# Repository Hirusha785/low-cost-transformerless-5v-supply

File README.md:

# Low-Cost Transformerless 5V Supply

A compact **non-isolated transformerless AC-to-5V DC power supply PCB** designed using KiCad.

This project uses a capacitive dropper circuit, bridge rectifier, smoothing capacitors, zener protection, and an LM7805 voltage regulator to generate a low-current 5V DC output.

> ⚠️ **High Voltage Warning:**  
> This is a **non-isolated mains-powered circuit**. The 5V output is **not safely isolated** from AC mains.  
> Do not touch the circuit while powered. Do not connect it to USB, computers, Arduino boards, ESP32 boards, oscilloscopes, or any user-accessible circuit unless proper isolation is added.

---

## Repository Description

A compact non-isolated transformerless AC-to-5V DC power supply PCB using a capacitive dropper, bridge rectifier, zener protection, 7805 regulator, and LED power indicator.

---

## Project Overview

This PCB demonstrates a low-cost transformerless power supply design suitable for learning, testing, and sealed low-power applications.

The circuit converts AC mains input into regulated 5V DC through the following stages:

1. Capacitive voltage/current dropping stage
2. Bridge rectifier stage
3. DC smoothing and filtering stage
4. Zener overvoltage protection stage
5. 7805 linear voltage regulation stage
6. LED power indication stage

---

## Features

- Low-cost transformerless AC-to-DC design
- Compact PCB layout
- 5V regulated DC output
- Bridge rectifier using 1N4007 diodes
- Zener diode voltage protection
- LM7805 / 7805 TO-220 voltage regulator
- LED power indicator
- Screw terminal AC input
- Screw terminal 5V DC output
- Through-hole component design
- Designed in KiCad

---

## Circuit Operation 

AC mains input is connected through J1.
C4 works as the capacitive dropper and limits the input current.
R3 discharges C4 after power is removed.
D1–D4 form the bridge rectifier and convert AC to DC.
C1 filters high-frequency noise.
C2 smooths the rectified DC voltage and reduces ripple.
D5 and D6 provide Zener voltage protection/clamping.
R1 and R2 help limit current in the protection stage.
U1 is the 7805 voltage regulator and provides regulated 5V DC output.
C5 smooths the final 5V output.
D7 and R4 work as the power indicator circuit.
Since this is a transformerless design, the output is not isolated from AC mains and must be handled carefully.

---

## Main Components

| Reference | Component | Description |
|---|---|---|
| J1 | Screw Terminal | AC input connector |
| C4 | 225k / 2.2uF Capacitor | Capacitive dropper capacitor |
| R3 | 1MΩ | Dropper capacitor discharge resistor |
| D1 | 1N4007 | Bridge rectifier diode |
| D2 | 1N4007 | Bridge rectifier diode |
| D3 | 1N4007 | Bridge rectifier diode |
| D4 | 1N4007 | Bridge rectifier diode |
| C1 | 0.1uF | Noise filtering capacitor |
| C2 | 1000uF | DC smoothing capacitor |
| D5 | Zener Diode | Voltage protection/clamping |
| D6 | Zener Diode | Voltage protection/clamping |
| R1 | 20kΩ | Protection/bias resistor |
| R2 | 20kΩ | Protection/bias resistor |
| U1 | LM7805 / 7805 TO-220 | 5V voltage regulator |
| C5 | 470uF | Output smoothing capacitor |
| D7 | LED | Power indicator |
| R4 | 2.2kΩ | LED current-limiting resistor |
| J2 | Screw Terminal | 5V DC output connector |

---

## PCB Design

The PCB was designed using KiCad and includes:

- Through-hole components
- AC input screw terminal
- 5V DC output screw terminal
- Compact board layout
- Top and bottom routing
- 3D model preview
- Power indicator LED
- Mounting holes

---

## Project Images

### Circuit Schematic

---

### PCB Layout

---

### 3D View

---

## Suitable Applications

This circuit may only be used in **sealed low-power applications**, such as:

- 💡 **Small indicator circuits**  
  For basic power indication or low-current status indication circuits inside closed equipment.

- 🔧 **Low-current control circuits**  
  For small internal control circuits where only a limited amount of current is required.

- 📦 **Enclosed appliance control boards**  
  Suitable only when the full PCB is mounted inside a properly insulated and sealed enclosure.

- 🎓 **Educational PCB design demonstrations**  
  Useful for learning about capacitive dropper supplies, rectification, filtering, zener protection, and basic voltage regulation.

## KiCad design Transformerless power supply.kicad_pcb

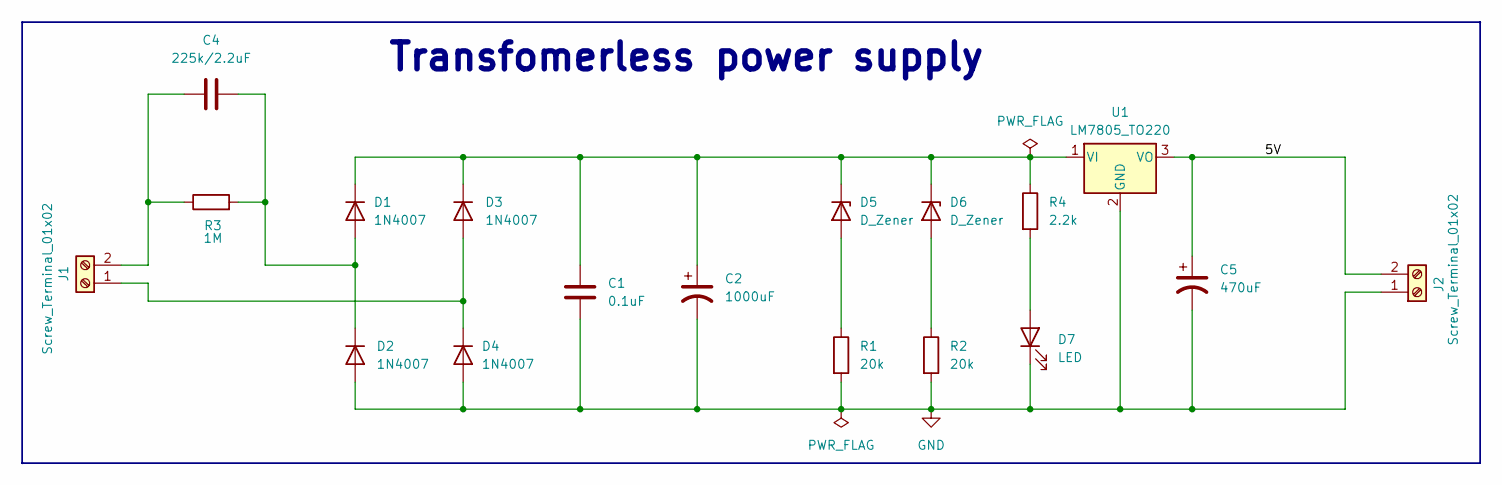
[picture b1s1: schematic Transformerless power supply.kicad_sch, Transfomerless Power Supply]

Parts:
C1: 0.1uF; C_Disc_D4.7mm_W2.5mm_P5.00mm
C2: 1000uF; CP_Radial_D10.0mm_P5.00mm
C4: 225k/2.2uF; C_Rect_L18.0mm_W6.0mm_P15.00mm_FKS3_FKP3
C5: 470uF; CP_Radial_D10.0mm_P5.00mm
D1, D2, D3, D4: 1N4007; D_DO-41_SOD81_P10.16mm_Horizontal
D5, D6: D_Zener; D_A-405_P7.62mm_Horizontal
D7: LED; LED_D5.0mm
J1, J2: Screw_Terminal_01x02; TerminalBlock_bornier-2_P5.08mm
R1, R2: 20k; R_Axial_DIN0207_L6.3mm_D2.5mm_P7.62mm_Horizontal
R3: 1M; R_Axial_DIN0207_L6.3mm_D2.5mm_P7.62mm_Horizontal
R4: 2.2k; R_Axial_DIN0207_L6.3mm_D2.5mm_P7.62mm_Horizontal
U1: LM7805_TO220; TO-220-3_Vertical

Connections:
/5V: C5.1, J2.2, U1.3 (VO)
GND: C1.2, C2.2, C5.2, D2.2 (A), D4.2 (A), D7.1 (K), J2.1, R1.2, R2.2, U1.2 (GND)
unnamed: C4.1, D1.2 (A), D2.1 (K), R3.2
unnamed: C1.1, C2.1, D1.1 (K), D3.1 (K), D5.1 (K), D6.1 (K), R4.1, U1.1 (VI)
unnamed: D3.2 (A), D4.1 (K), J1.1
unnamed: D5.2 (A), R1.1
unnamed: D6.2 (A), R2.1
unnamed: D7.2 (A), R4.2
unnamed: C4.2, J1.2, R3.1

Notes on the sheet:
Transfomerless power supply

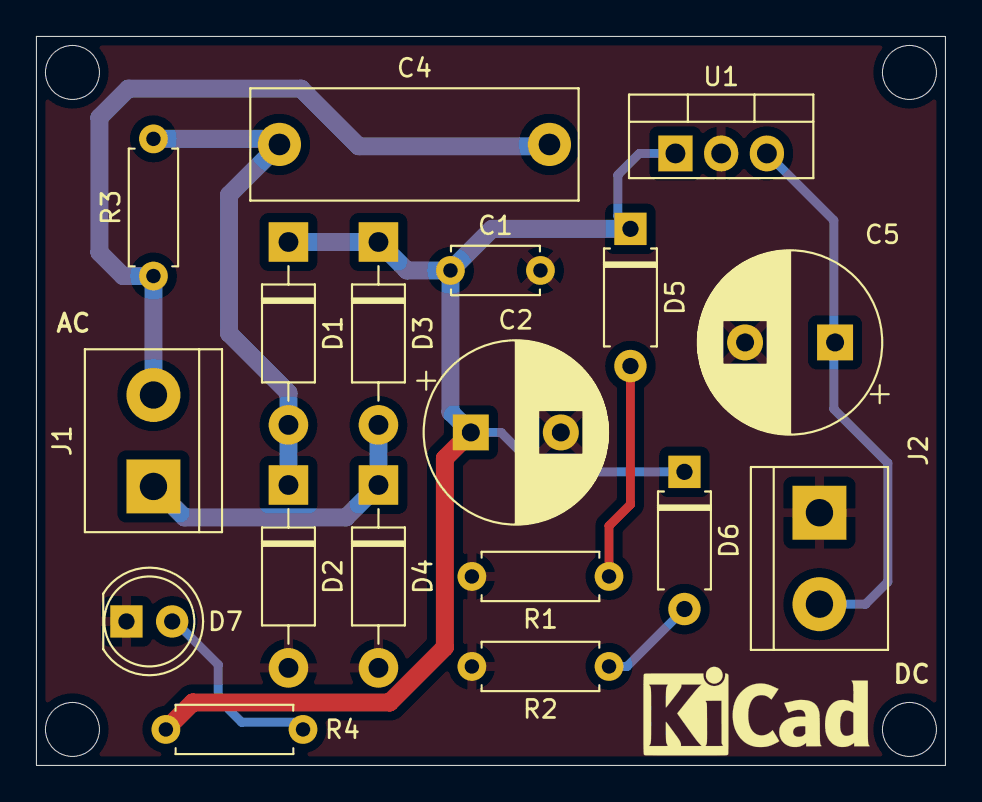
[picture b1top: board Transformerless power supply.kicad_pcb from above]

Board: 2 copper layers, 50.5 x 40.5 mm, 18 parts (0 on the bottom side), 9 nets.
